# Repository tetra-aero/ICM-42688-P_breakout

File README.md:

# ICM-42688-P_breakout
ICM-42688-P breakout board 

## Reference
1. https://product.tdk.com/ja/search/sensor/mortion-inertial/imu/info?part_no=ICM-42688-P
2. https://product.tdk.com/system/files/dam/doc/product/sensor/mortion-inertial/imu/data_sheet/ds-000347-icm-42688-p-v1.2.pdf

## Board
### Top

### Back

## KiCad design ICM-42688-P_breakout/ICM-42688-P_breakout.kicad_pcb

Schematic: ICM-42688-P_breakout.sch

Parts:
C1: 0.01uF; C_0603_1608Metric
C2: 0.1uF; C_0402_1005Metric
C3: 22uF; C_0603_1608Metric
IC1: ICM-42688-P; QFN50P300X250X97-14N; Manufacturer_Part_Number ICM-42688-P
J1, J2: Conn_01x04_Female; PinHeader_1x04_P2.54mm_Vertical

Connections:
unnamed: C1.1, C2.1, C3.1, IC1.5 (VDDIO), IC1.8 (VDD), J1.1
unnamed: C1.2, C2.2, C3.2, IC1.6 (GND), IC1.7 (RESV_3), IC1.11 (RESV_5), J2.1
unnamed: IC1.1 (AP_SDO/AP_AD0), J1.4
unnamed: IC1.4 (INT1/INT), J2.2
unnamed: IC1.9 (INT2/FSYNC/CLKIN), J2.3
unnamed: IC1.12 (AP_CS), J2.4
unnamed: IC1.13 (AP_SCL/AP_SCLK), J1.2
unnamed: IC1.14 (AP_SDA/AP_SDIO/AP_SDI), J1.3

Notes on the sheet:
4: SDO 3: SDI 2: SPC 1: VDD
1: GND 2: INT1 3: INT2 4: CS

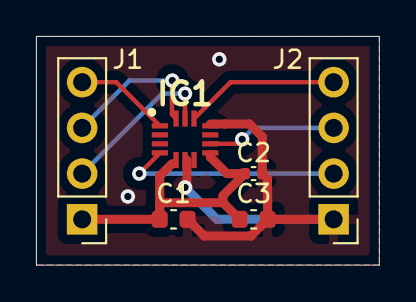
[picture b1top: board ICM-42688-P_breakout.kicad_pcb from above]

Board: 2 copper layers, 19.0 x 12.7 mm, 6 parts (0 on the bottom side), 8 nets.

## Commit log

2020-10-09 add parts ICM-42688-P from PCB Library Loader
    add parts ICM-42688-P from PCB Library Loader
2020-11-19 add schematic
    add schematic
2020-11-21 1st ordered to fusionPCB
    1st ordered to fusionPCB
2021-11-25 add readme, board photo
    add readme, board photo
2021-11-25 add readme, reference
    add readme, reference
